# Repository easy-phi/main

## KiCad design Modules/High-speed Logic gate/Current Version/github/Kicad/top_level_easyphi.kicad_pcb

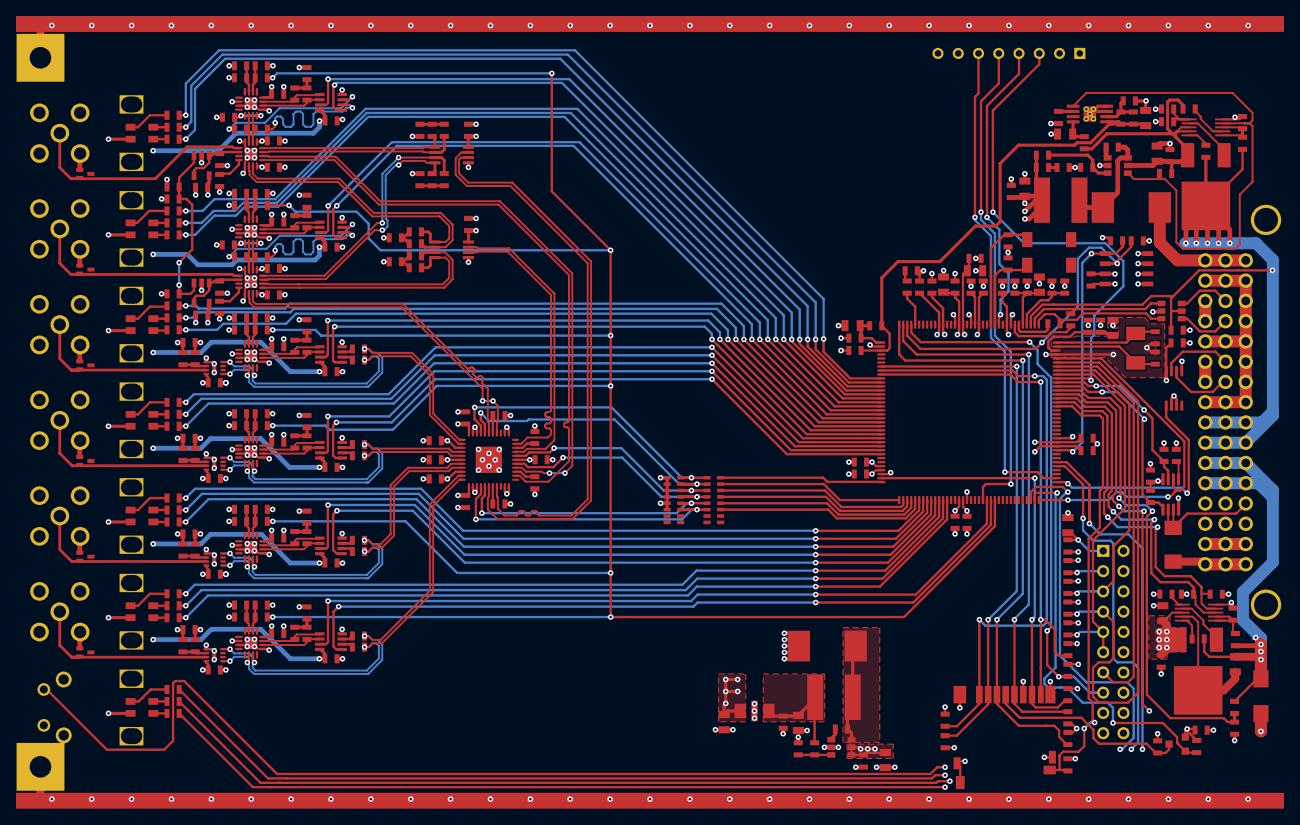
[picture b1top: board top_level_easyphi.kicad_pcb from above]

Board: 4 copper layers, 329 parts (0 on the bottom side), 243 nets.

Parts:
C1, C2: 1uF; SM0603_Capa
C3, C6, C18, C56, C57, C58, C59, C62, C63, C64, C65, C66, C67, C69, C71, C72, C73, C74, C75, C76, C77, C78, C79, C80, C81, C82, C83, C84, C85, C86, C87, C88, C89, C90, C91, C92: 10nF; SM0603_Capa
C4, C12, C19, C23, C37, C45, C52, C53: 10uF; SM0805
C5, C13, C22, C60, C68, C93: 22uF; SM0805
C7, C8, C9, C10, C11, C14, C17, C21, C24, C25, C26, C29, C30, C32, C33, C34, C35, C36, C38, C39, C40, C41, C42, C43, C44, C46, C49, C50, C51, C54, C55, C61, C70: 100nF; SM0603_Capa
C15, C16, C20: 1nF; SM0603_Capa
C27, C28, C31, C47, C48: 22pF; SM0603_Capa
D1: TVS 12V; TVS_SMAJ
D2: 3.3V TVS; TVS_SMLVT
D3, D6, D7, D8, D9, D11, D12: LED_RGB; CLV1A-FKB-CJ1M1F1BB7R4S3
D4, D19: MBRS340T3G; SCHOTTKY_MBRS340
D5, D10: LED; SM0603_Resistor
D13, D14, D15, D16, D17, D18: TVS_BIDIR; SC-75
FB1, FB2, FB3, FB4: FILTER; SM0603_Resistor
FB5: FILTER_ELKE333FA; Filter_ELK-E333FA
J1: JTAG_CONNEC; JTAG_20
J2: DM3D-SF(AS); DMD3D-SF
L1, L2: 2.2uH; IND_NR6028
P1: CONN_8; SIL-8
Q1: MOS_P; SOT23GDS
Q2, Q3: FDD8780; DPAKGDS
R1, R6, R15, R16, R27, R28, R29, R34, R35, R96, R105, R114, R123, R132, R141: 10k; SM0603_Resistor
R2, R3: 10; SM0603_Resistor
R4, R8: 2k; SM0603_Resistor
R5, R93, R94, R97, R102, R103, R106, R111, R112, R115, R120, R121, R124, R129, R130, R133, R138, R139, R142: 1k; SM0603_Resistor
R7: 390k; SM0603_Resistor
R9: 0.03; SM0805
R10: 270; SM0603_Resistor
R11: 120k; SM0603_Resistor
R12, R26, R43: 100; SM0603_Resistor
R13, R61, R95, R104, R113, R122, R131, R140: 12k; SM0603_Resistor
R14, R25: 6k8; SM0603_Resistor
R17, R18, R19, R20, R21, R22, R52: 100k; SM0603_Resistor
R23, R24: 39; SM0603_Resistor
R30, R31, R32, R33: 47k; SM0603_Resistor
R36, R38, R39, R40, R41, R42, R45, R47, R49, R51, R55, R56, R58, R60: 680; SM0603_Resistor
R37, R44, R46, R48, R50, R57, R59: 220; SM0603_Resistor
R53: 49k9; SM0603_Resistor
R54: 15k8; SM0603_Resistor
R62, R98, R107, R116, R125, R134, R143: 3k; SM0603_Resistor
R63, R64: 125; SM0603_Resistor
R65, R66, R69, R70, R75, R76, R81, R82, R83, R84, R100, R109, R118, R127, R136, R145: 19; SM0603_Resistor
R67, R68, R71, R72, R73, R74, R77, R78, R99, R101, R108, R110, R117, R119, R126, R128, R135, R137, R144, R146: 49.9; SM0603_Resistor
R79: 49.9k; SM0603_Resistor
R80: 23.4k; SM0603_Resistor
R85, R87, R89, R91: 249; SM0603_Resistor
R86, R88, R90, R92: 62; SM0603_Resistor
RP1, RP2: R_PACK8; RNETWORK8_0603
U1: MAX5924D; uMAX-uSOP_10
U2: MAX5925D; uMAX-uSOP_10
U3: 24LC64; SO8E
U4: USBLC6-2; SOT23_6
U5: TPS7A4901; MSOP_8_PP
U6, U33: AOZ1280; SOT23_6
U7: SAM3X8E; LQFP-144
U8: SN74LVC2G240DCTR; SM8
U9: SN65LVDM176DGK; MSOP_8
U10: 2-1825027-0
U11, U17, U18, U19, U20, U21, U23: RLP1-600-800
U12: TE-5650478-5
U13, U14: LM7321MF; SOT23-5-SN
U15, U16: TROU_FIX; TROU_FIX_FP
U22, U24, U25, U26, U27, U28: CONNEC_QMA_ANO_2622-4035; connec_QMA
U29, U30: SY89854U; QFN16
U31, U32: MC100LVEP05DTG; TSSOP-8_3x3mm
U34: SY89540U; QFN44
U35, U36, U37, U38: SY89850U; qfn8
U39, U41, U43, U45, U47, U49: NB4L52; QFN16
U40, U42, U44, U46, U48, U50: MAX9032AKA; SOT23_8
U51, U52, U53, U54: CARD_BORDER; card_border
X1: 12MHz; 7A-12MHz
X2: 32.768KHz; ABS25

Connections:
+2.5V: C54.1, C55.1, C56.1, C57.1, C58.1, C59.1, C62.1, C63.1, C65.1, C66.1, C67.1, C69.1, C71.1, C72.1, C73.1, C74.1, C75.1, C76.1, C77.1, C78.1, C79.1, C80.1, C81.1, C83.1, C85.1, C87.1, C89.1, C91.1, C93.1, FB5.3, R61.1, R63.2, R64.2, R85.1, R87.1, R89.1, R91.1, R95.1, R104.1, R113.1, R122.1, R131.1, R140.1, U13.5, U14.5, U29.8, U29.13, U30.8, U30.13, U31.8, U32.8, U34.6, U34.22, U34.25, U34.28, U34.31, U34.34, U35.8, U36.8, U37.8, U38.8, U39.2, U39.12, U41.2, U41.12, U43.2, U43.12, U45.2, U45.12, U47.2, U47.12, U49.2, U49.12
+3.3V: C9.1, C17.1, C19.1, C21.1, C22.1, C23.1, C24.1, C25.1, C26.1, C29.1, C30.1, C32.1, C33.1, C34.1, C49.1, C82.1, C84.1, C86.1, C88.1, C90.1, C92.1, D3.2, D6.2, D7.2, D8.2, D9.2, D11.2, D12.2, FB1.2, J1.1, J1.2, L2.2, P1.1, Q1.S, R4.1, R6.1, R8.1, R16.1, R17.1, R18.1, R19.1, R20.1, R21.1, R22.1, R26.2, R27.1, R28.1, R29.1, R30.1, R31.1, R32.1, R33.1, R34.1, R35.2, R52.1, R53.1, U3.8, U7.11, U7.52, U7.57, U7.62, U7.105, U7.125, U8.8, U9.8, U40.8, U42.8, U44.8, U46.8, U48.8, U50.8
+3.3VADC: C6.1, C12.1, C41.1, FB2.2, R13.1, U5.1, U7.75
+5V: C13.1, C14.1, FB4.1, Q2.S, R12.1, R15.1, U2.8, U2.9, U6.5
+12V: C5.1, C8.1, C60.1, C61.1, Q3.S, U1.8, U33.4, U33.5
/LogicGate/+2.5_RAW: C68.1, C70.1, FB5.1, L1.2, R79.1
/LogicGate/AND_Q: U31.7, U34.41
/LogicGate/AND_nQ: U31.6, U34.39
/LogicGate/ActivityDetector_In1/Activity: R93.2, U29.15, U39.6
/LogicGate/ActivityDetector_In1/VTActivity: R65.2, U39.5, U39.8
/LogicGate/ActivityDetector_In1/nActivity: R94.2, U29.14, U39.7
/LogicGate/ActivityDetector_In2/Activity: R138.2, U30.15, U49.6
/LogicGate/ActivityDetector_In2/VTActivity: R66.2, U49.5, U49.8
/LogicGate/ActivityDetector_In2/nActivity: R139.2, U30.14, U49.7
/LogicGate/ActivityDetector_Out1/Activity: R129.2, U34.23, U35.1, U47.6
/LogicGate/ActivityDetector_Out1/nActivity: R130.2, U34.24, U35.4, U47.7
/LogicGate/ActivityDetector_Out2/Activity: R120.2, U34.26, U36.1, U45.6
/LogicGate/ActivityDetector_Out2/nActivity: R121.2, U34.27, U36.4, U45.7
/LogicGate/ActivityDetector_Out3/Activity: R111.2, U34.29, U37.1, U43.6
/LogicGate/ActivityDetector_Out3/nActivity: R112.2, U34.30, U37.4, U43.7
/LogicGate/ActivityDetector_Out4/Activity: R102.2, U34.32, U38.1, U41.6
/LogicGate/ActivityDetector_Out4/nActivity: R103.2, U34.33, U38.4, U41.7
/LogicGate/CONFIG: RP1.13, U7.111
/LogicGate/IN1: D13.2, U22.5, U29.1
/LogicGate/IN1_Q1: R67.1, U29.12, U31.1
/LogicGate/IN1_Q2: U29.10, U34.4
/LogicGate/IN1_Q3: R68.1, U29.7, U32.2
/LogicGate/IN1_nQ1: R71.1, U29.11, U31.2
/LogicGate/IN1_nQ2: U29.9, U34.2
/LogicGate/IN1_nQ3: R72.1, U29.6, U32.1
/LogicGate/IN2: D14.2, U24.5, U30.1
/LogicGate/IN2_Q1: R73.1, U30.12, U31.3
/LogicGate/IN2_Q2: R74.1, U30.10, U32.4
/LogicGate/IN2_Q3: U30.7, U34.17
/LogicGate/IN2_nQ1: R77.1, U30.11, U31.4
/LogicGate/IN2_nQ2: R78.1, U30.9, U32.3
/LogicGate/IN2_nQ3: U30.6, U34.15
/LogicGate/LOAD: RP1.14, U7.110
/LogicGate/LX: C64.2, D19.2, L1.1, U33.6
/LogicGate/OR_Q: U32.6, U34.10
/LogicGate/OR_nQ: U32.7, U34.8
/LogicGate/OUT1: D15.2, U25.5, U35.7
/LogicGate/OUT2: D16.2, U26.5, U36.7
/LogicGate/OUT3: D17.2, U27.5, U37.7
/LogicGate/OUT4: D18.2, U28.5, U38.7
/template core easyphi/1.8V_uC: C37.1, C38.1, C39.1, C40.1, C42.1, C43.1, C44.1, FB3.1, U7.10, U7.45, U7.56, U7.61, U7.104, U7.124
/template core easyphi/5V_BP: C46.1, Q2.D, R2.1, R10.1, U4.5, U7.39, U12.A9, U12.A10, U12.B9, U12.B10, U12.C9, U12.C10
/template core easyphi/5V_PGOOD: R15.2, U2.4, U5.5, U6.4
/template core easyphi/12V_DETECT: R7.2, R11.1, U7.24
/template core easyphi/12V_EN: R1.1, U1.3, U7.22
/template core easyphi/12V_POK: R16.2, U1.4, U7.21
/template core easyphi/A18/SPI0_MISO/PA25: RP1.16, U7.108
/template core easyphi/A19/SPI0_MOSI/PA26: RP1.15, U7.109
/template core easyphi/AD0/NANDRDY/TIOA1/PA2: U7.85, U40.7
/template core easyphi/AD1/WKUP1/PWMFI1/TIOB1/PA3: R44.2, U7.84
/template core easyphi/AD2/NWAIT/TCLK1/PA4: R45.2, U7.83
/template core easyphi/AD3/NCS0/TIOB2/PA6: R39.1, U7.82
/template core easyphi/AD8/PWMH0/TWD1/PB12: U7.86, U40.1
/template core easyphi/AD9/PWMH1/TWCK1/PB13: R40.1, U7.87
/template core easyphi/AD10/PWML1/RF/PB17: R47.2, U7.88
/template core easyphi/AD11/PWML2/RD/PB18: R46.2, U7.89
/template core easyphi/AD12/PWML3/RK/PB19: U7.90, U50.7
/template core easyphi/AD13/SPI0_NPCS1/TXD2/PB20: U7.91, U50.1
/template core easyphi/AD14/WKUP13/SPI0_NPCS2/RXD2/PB21: R41.1, U7.92
/template core easyphi/CLK10_IN: U9.6, U12.B7
/template core easyphi/CLK_10M: U7.1, U9.1
/template core easyphi/ECOL/D11/PC13: U7.95, U48.7
/template core easyphi/ECRS/D8/PC10: U7.117, U44.7
/template core easyphi/ECRSDV/ERXDV/PB4: R56.1, U7.119
/template core easyphi/ERASE_ARD: P1.5, U7.130
/template core easyphi/ERX0/PB5: R60.2, U7.120
/template core easyphi/ERX1/PB6: R59.2, U7.121
/template core easyphi/ERX2/D9/PC11: R49.2, U7.93
/template core easyphi/ERX3/D10/PC12: R48.2, U7.94
/template core easyphi/ERXCK/D12/PC14: U7.96, U48.1
/template core easyphi/ETX0/PB2: R58.2, U7.115
/template core easyphi/ETX1/PB3: U7.118, U44.1
/template core easyphi/ETX2/D13/PC15: R42.1, U7.97
/template core easyphi/ETX3/D14/PC16: R51.2, U7.98
/template core easyphi/ETXCK/EREFCK/PB0: RP1.11, U7.113
/template core easyphi/ETXEN/PB1: R55.1, U7.114
/template core easyphi/ETXER/D15/PC17: R50.2, U7.99
/template core easyphi/EXT_SYNC1: D2.2, U8.2, U8.3, U12.A13
/template core easyphi/I2CSCL: R8.2, U3.6, U7.70
/template core easyphi/I2CSDA: R4.2, U3.5, U7.9
/template core easyphi/NRD/SPI0_NPCS1/PA29: RP1.12, U7.112
/template core easyphi/PWMH3/UTXD/PA9: P1.6, U7.2
/template core easyphi/PWMH4/NANDWE/PC20: U7.131, U42.7
/template core easyphi/PWMH5/NANDOE/PC19: U7.101, U46.1
/template core easyphi/PWMH6/NWE/NWR0/PC18: U7.100, U46.7
/template core easyphi/PWML1/D2/PC4: R57.2, U7.116
/template core easyphi/PWML4/NBS0/A10/PC21: U7.132, U42.1
/template core easyphi/PWML5/A1/PC22: R97.1, R106.1, R115.1, R124.1, R133.1, R142.1, U7.133
/template core easyphi/P_SD: Q1.G, R52.2, U7.143
/template core easyphi/RCB_1: D1.2, R3.1, R5.1, R7.1, R9.1, U12.A11, U12.A12, U12.B11, U12.B12, U12.C11, U12.C12
/template core easyphi/RCB_2: R5.2, U1.10
/template core easyphi/RST_ARD: P1.4, U7.47
/template core easyphi/SYNC_STATE: U7.32, U7.144, U8.6
/template core easyphi/SYNC_nOE: R34.2, U7.26, U8.7
/template core easyphi/SYNC_nRST: R6.2, U7.25, U8.1
/template core easyphi/USB_D+: R23.1, U4.3, U7.37
/template core easyphi/USB_D+_CON: U4.4, U12.B4
/template core easyphi/USB_D-: R24.1, U4.1, U7.38
/template core easyphi/USB_D-_CON: U4.6, U12.B3
/template core easyphi/USR_BUTTN: U7.142, U10.3
/template core easyphi/USR_LED1: R36.1, U7.5
/template core easyphi/USR_LED2: R37.2, U7.23
/template core easyphi/USR_LED3: R38.2, U7.6
/template core easyphi/VDD_PLL: C45.1, C51.1, FB3.2, U7.34
/template core easyphi/VMCI: C50.1, J2.4, Q1.D
/template core easyphi/WKUP4/PWMH0/URXD/PA8: P1.3, U7.27
/template core easyphi/nCLK_10M_CON: U9.7, U12.B6
/template core easyphi/uSD_DET: J2.10, R27.2, U7.20
GND: C1.2, C2.2, C3.2, C4.2, C5.2, C7.2, C8.2, C9.2, C10.2, C11.2, C12.2, C13.2, C14.2, C15.2, C16.2, C17.2, C19.2, C20.2, C21.2, C22.2, C23.2, C24.2, C25.2, C26.2, C27.1, C28.1, C29.2, C30.2, C31.2, C32.2, C33.2, C34.2, C35.2, C36.2, C37.2, C38.2, C39.2, C40.2, C41.2, C42.2, C43.2, C44.2, C45.2, C46.2, C47.1, C48.1, C49.2, C50.2, C51.2, C52.2, C53.2, C54.2, C55.2, C56.2, C57.2, C58.2, C59.2, C60.2, C61.2, C62.2, C63.2, C65.2, C66.2, C67.2, C68.2, C69.2, C70.2, C71.2, C72.2, C73.2, C74.2, C75.2, C76.2, C77.2, C78.2, C79.2, C80.2, C81.2, C82.2, C83.2, C84.2, C85.2, C86.2, C87.2, C88.2, C89.2, C90.2, C91.2, C92.2, C93.2, D1.1, D2.1, D4.1, D5.2, D10.2, D13.1, D14.1, D15.1, D16.1, D17.1, D18.1, D19.1, FB5.2, J1.4, J1.6, J1.8, J1.10, J1.12, J1.14, J1.16, J1.18, J1.20, J2.6, J2.9, J2.11, J2.12, J2.13, J2.14, P1.2, P1.8, R1.2, R11.2, R14.2, R25.1, R54.1, R62.2, R65.1, R66.1, R69.2, R70.2, R75.2, R76.2, R80.1, R81.1, R82.1, R83.1, R84.1, R86.2, R88.2, R90.2, R92.2, R96.2, R98.2, R100.2, R105.2, R107.2, R109.2, R114.2, R116.2, R118.2, R123.2, R125.2, R127.2, R132.2, R134.2, R136.2, R141.2, R143.2, R145.2, RP2.1, RP2.2, RP2.3, RP2.4, RP2.5, RP2.6, U1.5, U2.5, U3.1, U3.2, U3.3, U3.4, U3.7, U4.2, U5.3, U5.4, U5.9, U6.2, U7.12, U7.33, U7.44, U7.54, U7.58, U7.74, U7.106, U7.126, U8.4, U9.2, U9.3, U9.5, U10.1, U10.2, U10.4, U11.1, U11.2, U12.A1, U12.A2, U12.A3, U12.A4, U12.A5, U12.A6, U12.A7, U12.A8, U12.A15, U12.A16, U12.B1, U12.B2, U12.B5, U12.B8, U12.B15, U12.B16, U12.C1, U12.C2, U12.C3, U12.C4, U12.C5, U12.C6, U12.C7, U12.C8, U12.C14, U12.C15, U12.C16, U12.D1, U12.D2, U13.2, U14.2, U15.FIX, U16.FIX, U17.1, U17.2, U18.1, U18.2, U19.1, U19.2, U20.1, U20.2, U21.1, U21.2, U22.1, U22.2, U22.3, U22.4, U23.1, U23.2, U24.1, U24.2, U24.3, U24.4, U25.1, U25.2, U25.3, U25.4, U26.1, U26.2, U26.3, U26.4, U27.1, U27.2, U27.3, U27.4, U28.1, U28.2, U28.3, U28.4, U29.5, U29.16, U29.17, U30.5, U30.16, U30.17, U31.5, U32.5, U33.2, U34.12, U34.13, U34.20, U34.21, U34.35, U34.36, U34.43, U34.44, U34.45, U35.5, U35.9, U36.5, U36.9, U37.5, U37.9, U38.5, U38.9, U39.3, U39.9, U39.17, U40.4, U41.3, U41.9, U41.17, U42.4, U43.3, U43.9, U43.17, U44.4, U45.3, U45.9, U45.17, U46.4, U47.3, U47.9, U47.17, U48.4, U49.3, U49.9, U49.17, U50.4, U51.1, U52.1, U53.1, U54.1
unnamed: D12.4, R60.1
unnamed: D12.1, R56.2
unnamed: D12.3, R59.1
unnamed: D11.3, R57.1
unnamed: D11.4, R58.1
unnamed: D11.1, R55.2
unnamed: D7.3, R46.1
unnamed: D8.3, R48.1
unnamed: D8.1, R41.2
unnamed: D8.4, R49.1
unnamed: D9.4, R51.1
unnamed: D9.1, R42.2
unnamed: D9.3, R50.1
unnamed: D6.1, R39.2
unnamed: D6.3, R44.1
unnamed: D6.4, R45.1
unnamed: D7.4, R47.1
unnamed: D7.1, R40.2
unnamed: R21.2, U7.53
unnamed: J1.7, R19.2, U7.31
unnamed: J1.3, R17.2
unnamed: R23.2, U7.42
unnamed: D5.1, R26.1
unnamed: R12.2, U2.2
unnamed: J1.15, R22.2, U7.69
unnamed: J1.9, J1.11, R20.2, U7.28
unnamed: J1.5, R18.2, U7.29
unnamed: R35.1, U8.5
unnamed: R53.2, R54.2, U6.3
unnamed: C3.1, U5.6
unnamed: J2.5, R28.2, U7.71
unnamed: J2.7, R31.2, U7.107
unnamed: J2.1, R33.2, U7.80
unnamed: Q3.D, R9.2, U1.9
unnamed: C2.1, R3.2, U1.1, U1.2
unnamed: C11.1, U1.6
unnamed: D3.3, R37.1
unnamed: D10.1, R43.2
unnamed: R43.1, U7.68
unnamed: J1.13, U7.30
unnamed: C36.1, C53.1, FB2.1, U7.73
unnamed: C35.1, C52.1, FB1.1, U7.41
unnamed: C31.1, R25.2, U7.40
unnamed: C18.1, U6.1
unnamed: C18.2, D4.2, L2.1, U6.6
unnamed: Q3.G, U1.7
unnamed: R10.2, U2.10
unnamed: C4.1, FB4.2, U5.8
unnamed: C7.1, C10.1, U2.6
unnamed: Q2.G, U2.7
unnamed: C1.1, R2.2, U2.1, U2.3
unnamed: R24.2, U7.43
unnamed: J2.2, R32.2, U7.79
unnamed: J2.8, R30.2, U7.81
unnamed: J2.3, R29.2, U7.72
unnamed: C6.2, R13.2, R14.1, U5.2
unnamed: D3.4, R38.1
unnamed: D3.1, R36.2
unnamed: C27.2, U7.49, X2.4
unnamed: C28.2, U7.48, X2.1
unnamed: C48.2, U7.36, X1.1
unnamed: C47.2, U7.35, X1.2
unnamed: R89.2, R90.1, U37.6
unnamed: R87.2, R88.1, U36.6
unnamed: R81.2, U34.16
unnamed: R74.2, R76.1, R78.2
unnamed: R67.2, R69.1, R71.2
unnamed: R73.2, R75.1, R77.2
unnamed: R68.2, R70.1, R72.2
unnamed: R82.2, U34.9
unnamed: R84.2, U34.40
unnamed: R83.2, U34.3
unnamed: RP1.6, RP2.11, U34.37
unnamed: RP1.5, RP2.12, U34.38
unnamed: RP1.4, RP2.13, U34.5
unnamed: RP1.3, RP2.14, U34.7
unnamed: RP1.2, RP2.15, U34.18
unnamed: R85.2, R86.1, U35.6
unnamed: C16.1, U13.1, U13.4, U29.2
unnamed: R63.1, U29.4
unnamed: C15.1, R61.2, R62.1, U13.3, U14.3
unnamed: R91.2, R92.1, U38.6
unnamed: C64.1, U33.1
unnamed: R79.2, R80.2, U33.3
unnamed: C20.1, U14.1, U14.4, U30.2
unnamed: R64.1, U30.4
unnamed: RP1.1, RP2.16, U34.19
unnamed: R93.1, U40.3
unnamed: R97.2, R98.1, U39.14
unnamed: R101.1, U39.11, U40.5
unnamed: R99.1, U39.10, U40.6
unnamed: R95.2, R96.1, U39.15
unnamed: R94.1, U40.2
unnamed: R99.2, R100.1, R101.2
unnamed: R102.1, U42.3
unnamed: R106.2, R107.1, U41.14
unnamed: R110.1, U41.11, U42.5
unnamed: R108.1, U41.10, U42.6
unnamed: R104.2, R105.1, U41.15
unnamed: R103.1, U42.2
unnamed: R108.2, R109.1, R110.2
unnamed: R111.1, U44.3
unnamed: R119.1, U43.11, U44.5
unnamed: R117.1, U43.10, U44.6
unnamed: R112.1, U44.2
unnamed: R115.2, R116.1, U43.14
unnamed: R113.2, R114.1, U43.15
unnamed: R117.2, R118.1, R119.2
unnamed: R120.1, U46.3
unnamed: R128.1, U45.11, U46.5
unnamed: R126.1, U45.10, U46.6
unnamed: R121.1, U46.2
unnamed: R124.2, R125.1, U45.14
unnamed: R122.2, R123.1, U45.15
unnamed: R126.2, R127.1, R128.2
unnamed: R129.1, U48.3
unnamed: R133.2, R134.1, U47.14
unnamed: R137.1, U47.11, U48.5
unnamed: R135.1, U47.10, U48.6
unnamed: R131.2, R132.1, U47.15
unnamed: R130.1, U48.2
unnamed: R135.2, R136.1, R137.2
unnamed: R138.1, U50.3
unnamed: R142.2, R143.1, U49.14
unnamed: R146.1, U49.11, U50.5
unnamed: R144.1, U49.10, U50.6
unnamed: R140.2, R141.1, U49.15
unnamed: R139.1, U50.2
unnamed: R144.2, R145.1, R146.2

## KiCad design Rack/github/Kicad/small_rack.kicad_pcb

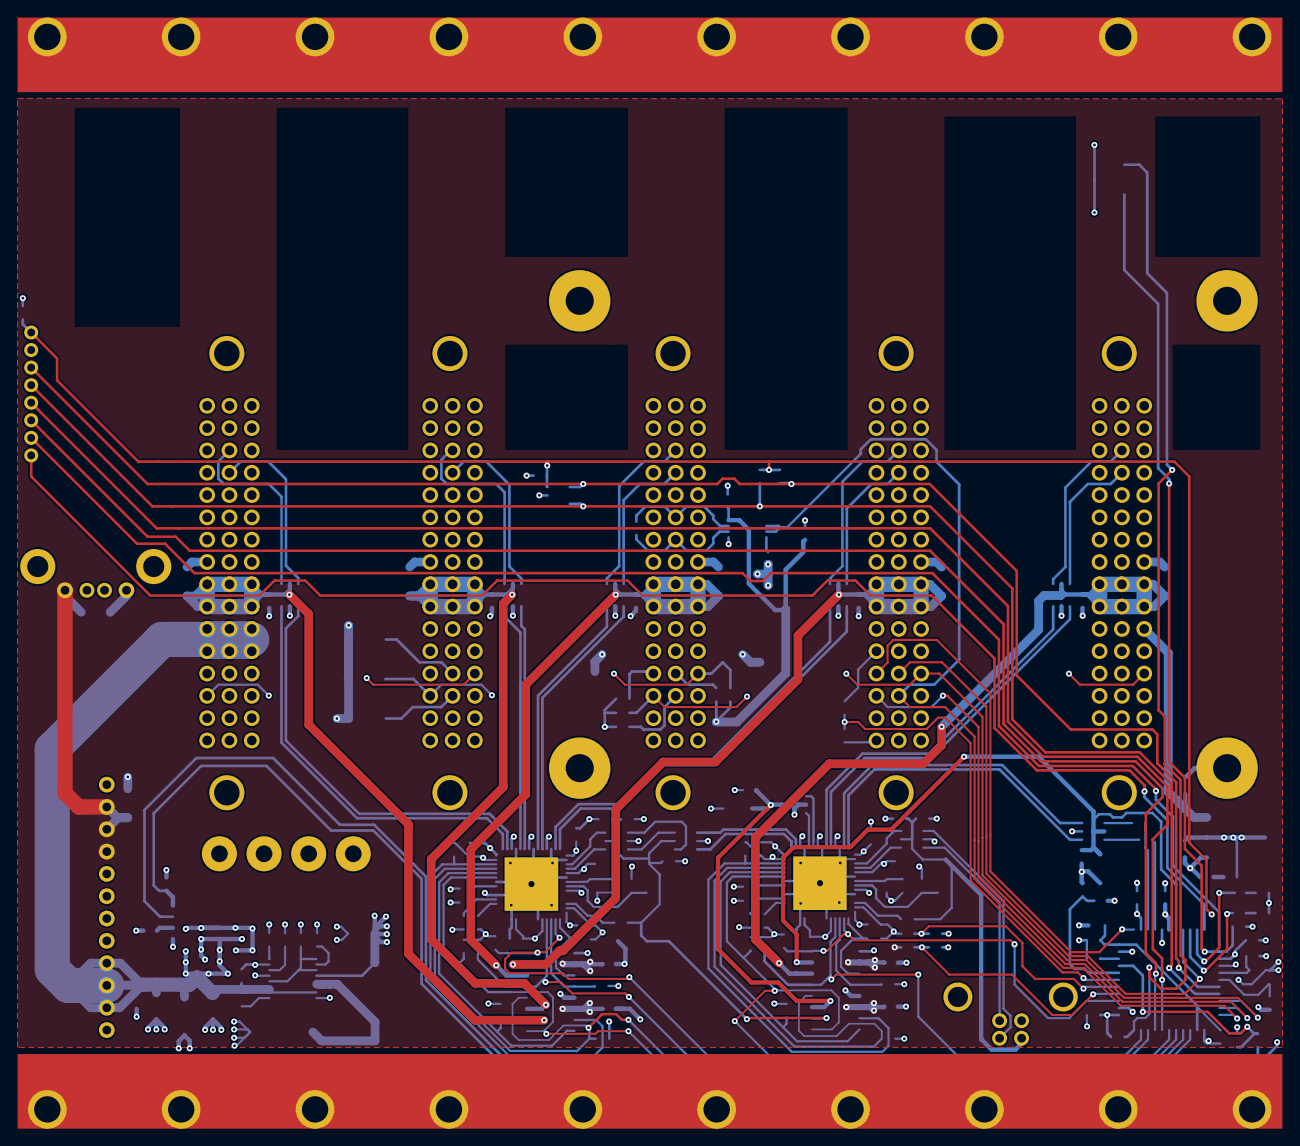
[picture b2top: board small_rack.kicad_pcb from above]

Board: 4 copper layers, 189 parts (0 on the bottom side), 120 nets.

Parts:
C1, C10, C11: 47uF; SM1210
C2, C4, C5, C7, C9, C12, C13, C14, C15, C21, C22, C23, C30, C31, C37, C38, C39, C46, C47, C48, C50, C51, C52, C55, C56, C57, C60, C61, C62, C64, C65, C66, C67: 100nF; SM0603_Capa
C3, C19, C24, C26, C28, C35, C40, C42, C44, C53: 100uF; SM1206
C6, C63: 1uF; SM0603_Capa
C8, C20, C25, C27, C29, C36, C41, C43, C45: 10nF; SM0603_Capa
C16, C32: 2.2uF; SM0603_Capa
C17, C18, C33, C34: 12pF; SM0603_Capa
C49, C54: 10uF; SM0805
C58, C59: 18pF; SM0603_Capa
D1: 12V TVS; TVS_SMAJ
D2, D3, D4, D5, D6: 3.3V TVS; TVS_SMLVT
D7: MBRS340T3G; SCHOTTKY_MBRS340
D8, D9, D10: LED; SM0603_Resistor
FB1: FILTER; SM0805
J1: MOLEX_0015244745
J2: USB_CONNEC; TE_292303-1
J1001, J1002, J1003, J1004, J1005, J1006, J1007, J1008, J1009, J1010, J1011, J1012, J1013, J1014, J1015, J1016, J1017, J1018, J1019, J1020: HOLE_BP; hole_bp
J1021, J1022: SLIDER; exposed_rack
K1: CONN_3; PAD_BL
L1: 10uH; CHOKE_DR1050
P1: CONN_8; TE-440054-8
R1, R2, R3, R4, R5, R37, R46, R47: 2k; SM0603_Resistor
R6, R18, R19, R31: 100k; SM0603_Resistor
R7, R8, R9, R10, R11, R12, R13, R14, R15, R16, R17, R20, R21, R22, R23, R24, R25, R26, R27, R28, R29, R30: 15k; SM0603_Resistor
R32: 100; SM0603_Resistor
R33, R40, R41: 4k7; SM0603_Resistor
R34: 14k; SM0603_Resistor
R35, R42, R43, R50: 30k; SM0603_Resistor
R36, R38, R39, R48, R49, R51: 10k; SM0603_Resistor
R44, R45: 22; SM0603_Resistor
U1: USB_CONNEC; AU-Y1007-R
U2, U3, U6, U7, U8: TE-8-1393640-3; 8-1393640-3
U4: R-535.0PA
U5: MAX1685; QSOP-16
U9: FOX924B
U10: SN65LVDM176DGK; MSOP_8
U11, U18: TPS2044BDR; TI-SOIC-16
U12, U19: CY7C65631-56LTXC; qfn_56_0.5
U13, U14, U15, U16, U17, U20, U21, U22, U23, U24: USBLC6-2; SOT23_6
U25: CUBIEBOARD; cubieboard
U26: NCP1117; SOT223
U27: LM73-0; SOT23_6
U28: ATMEGA32U4; TQFP44
U29: ACS713; SO8E
VAL: Logo
X1, X2: 24MHz; NX3225SA
X3: 16MHz; NX3225SA

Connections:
+3.3V: C10.1, C12.1, C13.1, C21.1, C22.1, C23.1, C37.1, C38.1, C46.1, C47.1, C50.1, C51.1, C52.1, L1.2, R1.2, R2.2, R3.2, R4.2, R5.2, R6.1, R7.1, R8.1, R9.1, R10.1, R11.1, R12.1, R13.1, R14.1, R15.1, R19.1, R20.1, R21.1, R22.1, R23.1, R24.1, R25.1, R26.1, R27.1, R28.1, R36.1, U5.12, U9.4, U10.8, U12.3, U12.7, U12.11, U12.15, U12.19, U12.23, U12.27, U12.33, U12.39, U12.55, U19.3, U19.7, U19.11, U19.15, U19.19, U19.23, U19.27, U19.33, U19.39, U19.55
+3.3VP: C55.1, C63.1, C67.1, P1.1, R40.1, R41.1, U27.3, U28.6
+5V: C3.1, C14.1, C30.1, C39.1, C48.1, C53.1, J2.1, R35.1, U4.9, U4.10, U4.11, U11.2, U11.6, U18.2, U18.6
+5VP: C54.1, C60.1, C61.1, C62.1, C65.1, FB1.2, R33.1, R42.1, R43.1, R50.1, U26.2, U26.4, U28.2, U28.14, U28.34, U29.8
+12V: C1.1, C2.1, C4.1, C5.1, C11.1, C49.1, D1.2, R34.1, U2.A11, U2.A12, U2.B11, U2.B12, U2.C11, U2.C12, U3.A11, U3.A12, U3.B11, U3.B12, U3.C11, U3.C12, U4.2, U4.3, U4.4, U5.2, U5.3, U5.15, U6.A11, U6.A12, U6.B11, U6.B12, U6.C11, U6.C12, U7.A11, U7.A12, U7.B11, U7.B12, U7.C11, U7.C12, U8.A11, U8.A12, U8.B11, U8.B12, U8.C11, U8.C12, U26.3, U29.3, U29.4
/CLK_10M: R32.2, U2.B7, U3.B7, U6.B7, U7.B7, U8.B7, U10.6
/monitoring/D+: R44.1, U20.6
/monitoring/D-: R45.1, U20.4
/monitoring/I2C_SCL: P1.3, R40.2, U27.4, U28.18
/monitoring/I2C_SDA: P1.4, R41.2, U27.6, U28.19
/monitoring/MON_AN0: R48.1, R49.1, U28.41
/monitoring/MON_AN1: R50.2, R51.1, U28.40
/monitoring/MON_AN4: R34.2, R37.1, U28.39
/monitoring/MON_AN5: R36.2, R39.1, U28.38
/monitoring/MON_AN6: R35.2, R38.1, U28.37
/monitoring/MON_PB1: R47.1, U28.9
/monitoring/MON_PB2: R46.1, U28.10
/monitoring/MON_PB3: P1.8, U28.11
/monitoring/MON_PB5: P1.5, U28.29
/monitoring/MON_PB6: P1.6, U28.30
/monitoring/MON_PB7: P1.7, U28.12
/nCLK_10M: R32.1, U2.B6, U3.B6, U6.B6, U7.B6, U8.B6, U10.7
/usb_hub2/USB_HOST_5V: C16.1, C44.1, C45.1, R17.2, R18.1, U15.5, U18.10, U24.5
/usb_hub2/USB_HOST_DM: U15.1, U24.4
/usb_hub2/USB_HOST_DP: U15.3, U24.6
/usb_hub2/USB_SL1_5V: C19.1, C20.1, U2.A9, U2.A10, U2.B9, U2.B10, U2.C9, U2.C10, U11.15, U13.5
/usb_hub2/USB_SL1_DM: U2.B3, U13.4
/usb_hub2/USB_SL1_DP: U2.B4, U13.6
/usb_hub2/USB_SL2_5V: C24.1, C25.1, U3.A9, U3.A10, U3.B9, U3.B10, U3.C9, U3.C10, U11.14, U14.5
/usb_hub2/USB_SL2_DM: U3.B3, U14.4
/usb_hub2/USB_SL2_DP: U3.B4, U14.6
/usb_hub2/USB_SL3_5V: C26.1, C27.1, U7.A9, U7.A10, U7.B9, U7.B10, U7.C9, U7.C10, U11.11, U16.5
/usb_hub2/USB_SL3_DM: U7.B3, U16.4
/usb_hub2/USB_SL3_DP: U7.B4, U16.6
/usb_hub2/USB_SL4_5V: C28.1, C29.1, U8.A9, U8.A10, U8.B9, U8.B10, U8.C9, U8.C10, U11.10, U17.5
/usb_hub2/USB_SL4_DM: U8.B3, U17.4
/usb_hub2/USB_SL4_DP: U8.B4, U17.6
/usb_hub/USB_HOST_5V: C32.1, R30.2, R31.1, U1.1, U22.5
/usb_hub/USB_HOST_DM: U1.2, U22.1
/usb_hub/USB_HOST_DP: U1.3, U22.3
/usb_hub/USB_SL1_5V: C35.1, C36.1, U18.15, U20.5, U28.7
/usb_hub/USB_SL2_5V: C40.1, C41.1, U6.A9, U6.A10, U6.B9, U6.B10, U6.C9, U6.C10, U18.14, U21.5
/usb_hub/USB_SL2_DM: U6.B3, U21.4
/usb_hub/USB_SL2_DP: U6.B4, U21.6
/usb_hub/USB_SL3_5V: C42.1, C43.1, U18.11, U23.5
/usb_hub/USB_SL3_nOVR: R22.2, U18.12, U19.53
GND: C1.2, C2.2, C3.2, C5.2, C6.2, C7.2, C8.2, C9.2, C10.2, C11.2, C12.2, C13.2, C14.2, C15.2, C16.2, C17.2, C18.2, C19.2, C20.2, C21.2, C22.2, C23.2, C24.2, C25.2, C26.2, C27.2, C28.2, C29.2, C30.2, C31.2, C32.2, C33.2, C34.2, C35.2, C36.2, C37.2, C38.2, C39.2, C40.2, C41.2, C42.2, C43.2, C44.2, C45.2, C46.2, C47.2, C48.2, C49.2, C50.2, C51.2, C52.2, C53.2, C54.2, C55.2, C56.2, C57.2, C58.2, C59.2, C60.2, C61.2, C62.2, C63.2, C64.2, C65.2, C66.2, C67.2, D1.1, D2.1, D3.1, D4.1, D5.1, D6.1, D7.1, D8.2, D9.2, D10.2, J1.3, J1.4, J2.4, J2.5, J2.6, J1001.1, J1002.1, J1003.1, J1004.1, J1005.1, J1006.1, J1007.1, J1008.1, J1009.1, J1010.1, J1011.1, J1012.1, J1013.1, J1014.1, J1015.1, J1016.1, J1017.1, J1018.1, J1019.1, J1020.1, J1021.1, J1022.1, K1.1, P1.2, R16.2, R18.2, R29.2, R31.2, R37.2, R38.2, R39.2, R49.2, R51.2, U1.4, U1.5, U1.6, U2.A1, U2.A2, U2.A3, U2.A4, U2.A5, U2.A6, U2.A7, U2.A8, U2.A15, U2.A16, U2.B1, U2.B2, U2.B5, U2.B8, U2.B15, U2.B16, U2.C1, U2.C2, U2.C3, U2.C4, U2.C5, U2.C6, U2.C7, U2.C8, U2.C14, U2.C15, U2.C16, U2.D1, U2.D2, U3.A1, U3.A2, U3.A3, U3.A4, U3.A5, U3.A6, U3.A7, U3.A8, U3.A15, U3.A16, U3.B1, U3.B2, U3.B5, U3.B8, U3.B15, U3.B16, U3.C1, U3.C2, U3.C3, U3.C4, U3.C5, U3.C6, U3.C7, U3.C8, U3.C14, U3.C15, U3.C16, U3.D1, U3.D2, U4.5, U4.6, U4.7, U4.8, U5.5, U5.7, U5.16, U6.A1, U6.A2, U6.A3, U6.A4, U6.A5, U6.A6, U6.A7, U6.A8, U6.A15, U6.A16, U6.B1, U6.B2, U6.B5, U6.B8, U6.B15, U6.B16, U6.C1, U6.C2, U6.C3, U6.C4, U6.C5, U6.C6, U6.C7, U6.C8, U6.C14, U6.C15, U6.C16, U6.D1, U6.D2, U7.A1, U7.A2, U7.A3, U7.A4, U7.A5, U7.A6, U7.A7, U7.A8, U7.A15, U7.A16, U7.B1, U7.B2, U7.B5, U7.B8, U7.B15, U7.B16, U7.C1, U7.C2, U7.C3, U7.C4, U7.C5, U7.C6, U7.C7, U7.C8, U7.C14, U7.C15, U7.C16, U7.D1, U7.D2, U8.A1, U8.A2, U8.A3, U8.A4, U8.A5, U8.A6, U8.A7, U8.A8, U8.A15, U8.A16, U8.B1, U8.B2, U8.B5, U8.B8, U8.B15, U8.B16, U8.C1, U8.C2, U8.C3, U8.C4, U8.C5, U8.C6, U8.C7, U8.C8, U8.C14, U8.C15, U8.C16, U8.D1, U8.D2, U9.2, U10.5, U11.1, U11.5, U12.4, U12.8, U12.12, U12.16, U12.20, U12.24, U12.28, U12.34, U12.40, U12.47, U12.50, U12.56, U12.57, U13.2, U14.2, U15.2, U16.2, U17.2, U18.1, U18.5, U19.4, U19.8, U19.12, U19.16, U19.20, U19.24, U19.28, U19.34, U19.40, U19.47, U19.50, U19.56, U19.57, U20.2, U21.2, U22.2, U23.2, U24.2, U25.1, U25.2, U25.3, U25.4, U26.1, U27.2, U28.5, U28.15, U28.23, U28.35, U28.43, U29.5, X1.2, X1.4, X2.2, X2.4, X3.2, X3.4
MON_DIG1: R11.2, U11.16, U12.30, U28.28
MON_DIG2: R10.2, U11.13, U12.32, U28.27
MON_DIG3: R9.2, U11.12, U12.53, U28.26
MON_DIG4: R8.2, U11.9, U12.51, U28.25
MON_DIG5: R24.2, U18.16, U19.30, U28.36
MON_DIG6: R23.2, U18.13, U19.32, U28.32
MON_DIG7: R21.2, U18.9, U19.51, U28.31
MON_DIG8: D2.2, R5.1, U2.B14, U3.B14, U6.B14, U7.B14, U8.B14, U10.2, U10.3, U28.22
MON_DIG9: D3.2, R4.1, U2.A14, U3.A14, U6.A14, U7.A14, U8.A14, U28.21
MON_DIG10: D4.2, R3.1, U2.C13, U3.C13, U6.C13, U7.C13, U8.C13, U28.20
MON_DIG11: D5.2, R2.1, U2.B13, U3.B13, U6.B13, U7.B13, U8.B13, U28.8
MON_DIG12: D6.2, R1.1, U2.A13, U3.A13, U6.A13, U7.A13, U8.A13, U28.1
unnamed: C9.1, U5.10
unnamed: U9.3, U10.4
unnamed: C7.1, U5.6
unnamed: D7.2, L1.1, U5.13, U5.14
unnamed: C8.1, U5.8
unnamed: C6.1, U5.4, U5.9, U5.11
unnamed: C4.2, U5.1
unnamed: R17.1, U12.26
unnamed: R7.2, U12.45
unnamed: R16.1, U12.49
unnamed: C15.1, R6.2, U12.46
unnamed: C17.1, U12.21, X1.1
unnamed: C18.1, U12.22, X1.3
unnamed: U12.18, U15.4
unnamed: U12.17, U15.6
unnamed: U12.10, U14.1
unnamed: U12.14, U13.1
unnamed: U12.13, U13.3
unnamed: U12.9, U14.3
unnamed: U12.6, U16.1
unnamed: U12.5, U16.3
unnamed: U12.2, U17.1
unnamed: R13.2, U11.7, U12.54
unnamed: R14.2, U11.4, U12.31
unnamed: R15.2, U11.3, U12.29
unnamed: U12.1, U17.3
unnamed: R12.2, U11.8, U12.52
unnamed: R30.1, U19.26
unnamed: R20.2, U19.45
unnamed: R29.1, U19.49
unnamed: C31.1, R19.2, U19.46
unnamed: C33.1, U19.21, X2.1
unnamed: C34.1, U19.22, X2.3
unnamed: U19.18, U22.4
unnamed: U19.17, U22.6
unnamed: U19.10, U21.1
unnamed: U19.14, U20.1
unnamed: U19.13, U20.3
unnamed: U19.9, U21.3
unnamed: U19.6, U23.1
unnamed: U19.5, U23.3
unnamed: U19.2, U24.1
unnamed: R26.2, U18.7, U19.54
unnamed: R27.2, U18.4, U19.31
unnamed: R28.2, U18.3, U19.29
unnamed: U19.1, U24.3
unnamed: R25.2, U18.8, U19.52
unnamed: K1.2, R42.2, U28.13
unnamed: R44.2, U28.4
unnamed: R45.2, U28.3
unnamed: C56.1, C57.1, FB1.1, U28.24, U28.44
unnamed: C64.1, U28.42
unnamed: C59.1, U28.17, X3.3
unnamed: K1.3, R43.2, U28.33
unnamed: C58.1, U28.16, X3.1
unnamed: R48.2, U29.7
unnamed: D8.1, R33.2
unnamed: C66.1, U29.6
unnamed: D9.1, R46.2
unnamed: D10.1, R47.2
VCC: J1.1, J1.2, U29.1, U29.2

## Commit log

2013-10-08 initial Rack commit
2013-10-08 commit lib
2013-10-08 common template push
2013-10-22 update on template
2013-10-22 fw delete
2013-10-23 Logo on rack
2013-10-23 Check rack
2013-10-23 update dir
2013-10-23 Push updated rack
2013-10-23 update push rack
2013-10-23 clean kicad_lib
2013-10-23 clean common template
2013-10-23 clean template!
2013-10-23 final update common template
2013-10-23 update lib
2014-01-02 update rack
2014-01-02 update common template
2014-01-02 update firmware template module
2014-01-02 add low cost dual discriminators
2014-01-02 adding dual 10mhz
2014-01-02 update fw 10mhz
2014-01-02 add delay lines
2014-03-13 update delay lines
2014-03-13 update counters
2014-03-13 update discriminators
2014-03-13 Adding high speed logic gate
2014-03-18 adding single host adapter
2014-03-26 updated files
2014-04-16 update firmwares
2014-04-17 update specs
2014-04-17 cleaning scpi output
2014-04-25 various minus updates
2014-05-13 firmware updates
2014-05-14 adding pulse generator
2015-02-04 current rack files

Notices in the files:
Modules/High-speed Logic gate/Current Version/github/Kicad/top_level_easyphi.kicad_pcb:
Licensed under CERN OHL V1.2
Rack/github/Kicad/small_rack.kicad_pcb:
CERN OHL
